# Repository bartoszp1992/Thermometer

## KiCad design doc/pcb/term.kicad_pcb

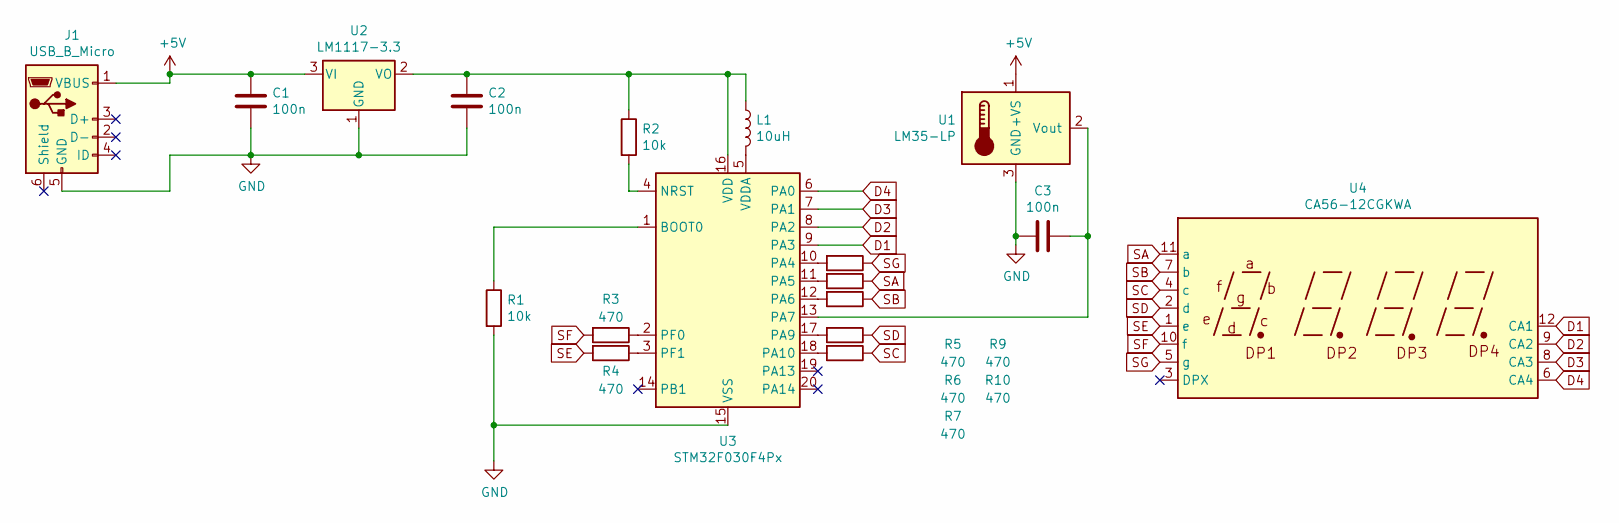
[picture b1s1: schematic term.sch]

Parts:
C1: 100n; C_Disc_D10.5mm_W5.0mm_P5.00mm
C2, C3: 100n; C_Disc_D8.0mm_W5.0mm_P7.50mm
J1: USB_B_Micro; USB_Micro-B_Molex_47346-0001
L1: 10uH; R_Axial_DIN0207_L6.3mm_D2.5mm_P10.16mm_Horizontal
R1, R2: 10k; R_Axial_DIN0207_L6.3mm_D2.5mm_P10.16mm_Horizontal
R3, R4, R5, R6, R7, R9, R10: 470; R_Axial_DIN0207_L6.3mm_D2.5mm_P10.16mm_Horizontal
U1: LM35-LP; TO-92
U2: LM1117-3.3; TO-252-2
U3: STM32F030F4Px; TSSOP-20_4.4x6.5mm_P0.65mm
U4: CA56-12CGKWA

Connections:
+5V: C1.1, J1.1 (VBUS), U1.1 (+VS), U2.3 (VI)
D1: U3.9 (PA3), U4.12 (CA1)
D2: U3.8 (PA2), U4.9 (CA2)
D3: U3.7 (PA1), U4.8 (CA3)
D4: U3.6 (PA0), U4.6 (CA4)
GND: C1.2, C2.2, C3.2, J1.5 (GND), R1.2, U1.3 (GND), U2.1 (GND), U3.15 (VSS)
unnamed: C2.1, L1.1, R2.1, U2.2 (VO), U3.16 (VDD)
unnamed: C3.1, U1.2 (Vout), U3.13 (PA7)
unnamed: L1.2, U3.5 (VDDA)
unnamed: R1.1, U3.1 (BOOT0)
unnamed: R2.2, U3.4 (NRST)
unnamed: R3.1, U3.2 (PF0)
unnamed: R4.1, U3.3 (PF1)
unnamed: R5.2, U3.10 (PA4)
unnamed: R6.2, U3.11 (PA5)
unnamed: R7.2, U3.12 (PA6)
unnamed: R9.2, U3.17 (PA9)
unnamed: R10.2, U3.18 (PA10)
SA: R6.1, U4.11 (a)
SB: R7.1, U4.7 (b)
SC: R10.1, U4.4 (c)
SD: R9.1, U4.2 (d)
SE: R4.2, U4.1 (e)
SF: R3.2, U4.10 (f)
SG: R5.1, U4.5 (g)

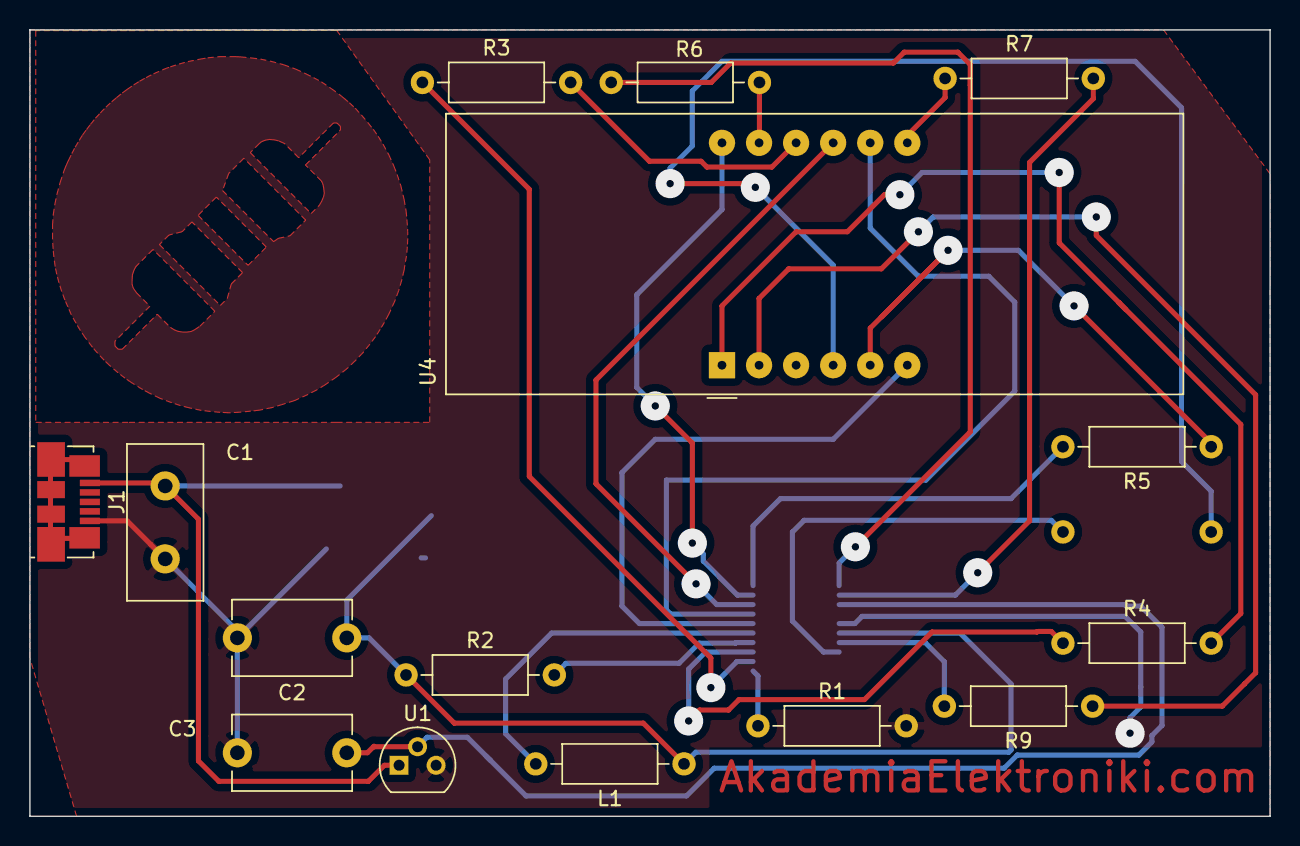
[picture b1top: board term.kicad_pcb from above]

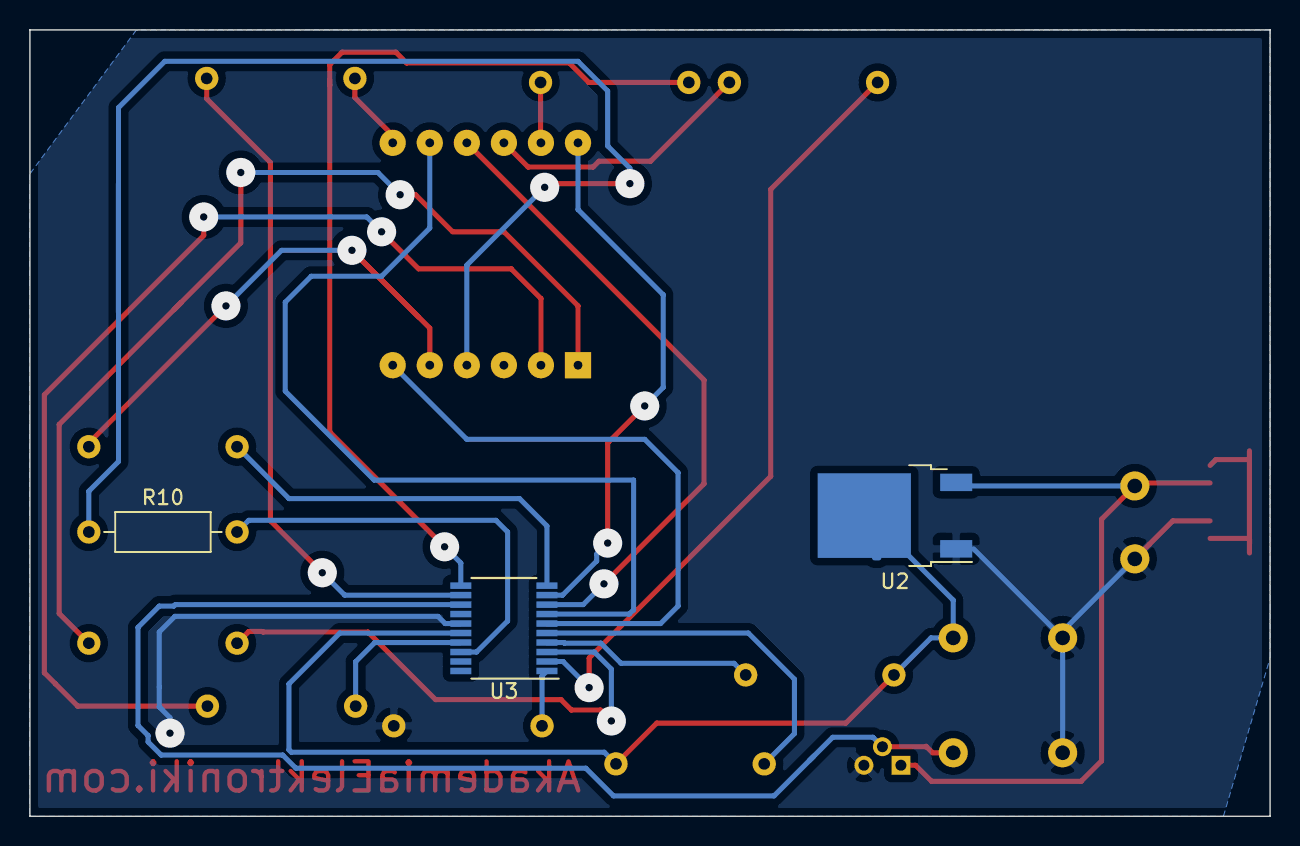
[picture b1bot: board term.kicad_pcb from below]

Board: 2 copper layers, 85.0 x 53.9 mm, 18 parts (3 on the bottom side), 25 nets.

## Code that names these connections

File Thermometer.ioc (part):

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Mcu.Name=STM32F030F4Px
Mcu.Package=TSSOP20
Mcu.UserName=STM32F030F4Px
PA0.GPIOParameters=GPIO_Label
PA0.GPIO_Label=D4
PA0.Signal=GPIO_Output
PA1.GPIOParameters=GPIO_Label
PA1.GPIO_Label=D3
PA1.Signal=GPIO_Output
PA10.GPIOParameters=GPIO_Label
PA10.GPIO_Label=SC
PA10.Signal=GPIO_Output
PA2.GPIOParameters=GPIO_Label
PA2.GPIO_Label=D2
PA2.Signal=GPIO_Output
PA3.GPIOParameters=GPIO_Label
PA3.GPIO_Label=D1
PA3.Signal=GPIO_Output
PA4.GPIOParameters=GPIO_Label
PA4.GPIO_Label=SG
PA4.Signal=GPIO_Output
PA5.GPIOParameters=GPIO_Label
PA5.GPIO_Label=SA
PA5.Signal=GPIO_Output
PA6.GPIOParameters=GPIO_Label
PA6.GPIO_Label=SB
PA6.Signal=GPIO_Output
PA7.Mode=IN7
PA7.Signal=ADC_IN7
PA9.GPIOParameters=GPIO_Label
PA9.GPIO_Label=SD
PA9.Signal=GPIO_Output
PF0-OSC_IN.GPIOParameters=GPIO_Label
PF0-OSC_IN.GPIO_Label=SF
PF0-OSC_IN.Signal=GPIO_Output
PF1-OSC_OUT.GPIOParameters=GPIO_Label
PF1-OSC_OUT.GPIO_Label=SE
PF1-OSC_OUT.Signal=GPIO_Output
RCC.SYSCLKFreq_VALUE=8000000
board=custom

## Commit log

2019-08-03 initial release
2019-08-04 pcb with logo
2019-08-04 new loc
2019-08-07 new pcb as credit card
2019-08-11 little details
2019-08-16 little pcb corrections
2019-08-26 cube project update
